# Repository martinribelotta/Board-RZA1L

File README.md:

RZ/A1L Board
============

Cortex-A9 board for Renesas RZ CPU using KiCAD

Hardware
--------

 - **CPU**: RZ/A1L 208LQFP
 - **RAM**: 32/64M sdram
 - **Flash**: 16/32M QSPI FLASH
 - **VGA**: 24bpp@\<TBD\>Hz
 - **USB**: 1 Host & 1 Dev
 - **GPIO**: 30 GPIO (+6 LED +2 Button) Muxed with:

Block Diagram
-------------

Schematic
---------

Preview
-------

Top view

Bottom view

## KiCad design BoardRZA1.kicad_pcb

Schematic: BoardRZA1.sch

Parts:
C1, C2, C3, C4, C5, C6, C7, C8, C11, C13, C14, C15, C16, C17, C18, C19, C21, C23, C24, C25, C26, C28, C29, C30, C31, C32, C33, C34, C35, C38, C39, C40, C41, C42, C43, C44, C45, C51, C52: 100n; C_0805
C36, C37: 10p; C_0805
C46, C50, C53: 1u; C_0805
C48, C67, C68, C69, C70, C71: 10u; C_0805
C72, C73, C74, C75, C76: 100p; C_0805
CON1: USB-MINI-B; USB_MINI_B
CON2: USB-A-PCB; USB_A_Vertical
CON3: microSD
D1, D2, D3, D4, D7, D8: LED; LED-0805
L1, L2, L3, L4, L5, L6, L7, L8, L9: BLM18PG600; SM0805
P1: CONN_02X04; Pin_Header_Straight_2x04
P2, P3, P4, P5, P6, P7, P8, P9, P10, P11, P12, P13, P14, P15, P16, P17: CONN_1; PINTST
P18, P19: CONN_01X40; Pin_Header_Straight_2x20
R1: 5K6; R_0805
R2, R3, R51: 220R; R_0805
R4, R5, R6, R7, R8, R9, R10, R11, R12, R19, R20, R22, R23, R42, R43, R44, R50: 10k; R_0805
R27, R45, R46, R47, R48: 1k; R_0805
SW1: RESET; RigthAnglePush
SW2: NMI; RigthAnglePush
SW3: SW0; RigthAnglePush
SW4: SW1; RigthAnglePush
U1: RZ-A1L; PQFP208
U2: 13MHz; OSC_2x2p5
U3: 48MHz; OSC_4PIN
U4: N25QXXX; SOP2-8
U5: AS4C16M16S; TSOP_II_54
U6: NCP1117ST33T3G; sot223
U7: BU42xx; SSOP-5
U9: NCP1117ST12T3G; sot223
X1: 32.768k; Crystal_Round_Vertical_3mm

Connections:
+1.2V: C50.1, L5.2, L6.2, L7.2, L8.2, L9.2, P9.1, U9.2 (VO)
+3.3V: C34.1, C35.1, C38.1, C39.1, C40.1, C41.1, C42.1, C43.1, C44.1, C45.1, C46.1, C51.1, C72.1, CON3.4 (VDD), D1.2 (K), D2.2 (K), D3.2 (K), D4.2 (K), D7.2 (K), D8.2 (K), L1.1, L2.1, L3.1, L4.1, P6.1, P18.3, P18.4, P18.37, P18.38, P19.3, P19.4, P19.37, P19.38, R4.1, R5.1, R6.1, R7.1, R8.1, R11.1, R19.1, R20.2, R22.1, R42.2, R43.2, R44.2, U2.4 (VCC), U3.4 (VCC), U4.8 (VCC), U5.1 (VDD), U5.3 (VDDQ), U5.9 (VDDQ), U5.14 (VDD), U5.27 (VDD), U5.43 (VDDQ), U5.49 (VDDQ), U6.2 (VO), U7.2 (Vdd), U9.3 (VI)
/+5v: C48.1, CON1.1 (VBUS), CON2.1 (VBUS), P2.1, U1.169 (VBUSIN1), U1.176 (VBUSIN0), U6.3 (VI)
/AVcc: C3.1, C33.2, L2.2, U1.102 (AVCC), U1.104 (AVref)
/DM_CLK: R10.2, U1.81 (P0_2/MD_CLK/RxD1/IRQ7)
/D_D+: CON1.3 (D+), U1.175 (DP0)
/D_D-: CON1.2 (D-), U1.174 (DM0)
/H_D+: CON2.3 (D+), U1.168 (DP1)
/H_D-: CON2.2 (D-), U1.167 (DM1)
/JTAG_TCK: P1.2, R7.2, U1.117 (TCK)
/JTAG_TDI: P1.6, R8.2, U1.115 (JP0_0/TDI)
/JTAG_TDO: P1.4, R5.2, U1.114 (JP0_1/TDO)
/JTAG_TMS: P1.1, R4.2, U1.116 (TMS)
/JTAG_TRST: P1.8, R6.2, R50.2, U1.113 (TRST)
/LCD_DATA0: P18.19, U1.192 (P8_0/LCD0_DATA0/ET_TXD0/SSISCK1/SCK3)
/LCD_DATA1: P18.20, U1.194 (P8_1/LCD0_DATA1/ET_TXD1/SSIWS1/RxD3)
/LCD_DATA2: P18.21, U1.198 (P8_2/LCD0_DATA2/ET_TXD2/SSITxD1/TxD3)
/LCD_DATA3: P18.22, U1.199 (P8_3/LCD0_DATA3/ET_TXD3/SSIRxD1)
/LCD_DATA4: P18.23, U1.200 (P8_4/LCD0_DATA4/ET_TXCLK/CTS2/TIOC0A)
/LCD_DATA5: P18.24, U1.201 (P8_5/LCD0_DATA5/ET_TXER/RTS2/TIOC0B)
/LCD_DATA6: P18.31, U1.27 (P8_6/LCD0_DATA6/ET_TXEN/IRQ6/CTS1/TIOC0C)
/LCD_DATA7: P18.32, U1.28 (P8_7/LCD0_DATA7/ET_RXD0/IRQ7/RTS1/TIOC0D)
/LCD_DATA8: P18.25, U1.17 (P6_0/D16/LCD0_DATA8/RSPCK0/TCLKA/WDTOVF)
/LCD_DATA9: P18.26, U1.19 (P6_1/D17/LCD0_DATA9/SSL00/TCLKB)
/LCD_DATA10: P18.27, U1.20 (P6_2/D18/LCD0_DATA10/MOSI0/TCLKC)
/LCD_DATA11: P18.28, U1.22 (P6_3/D19/LCD0_DATA11/MISO0/TCLKD)
/LCD_DATA12: P18.29, U1.24 (P6_4/D20/LCD0_DATA12/SSISCK3/MLB_CLK)
/LCD_DATA13: P18.30, U1.26 (P6_5/D21/LCD0_DATA13/SSIWS3/MLB_SIG)
/LCD_DATA14: P18.35, U1.31 (P6_6/D22/LCD0_DATA14/SSITxD3/MLB_DAT)
/LCD_DATA15: P18.36, U1.32 (P6_7/D23/LCD0_DATA15/SSIRxD3/IRQ0/TIOC3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)
/LCD_DATA16: P19.5, U1.33 (P6_8/D24/LCD0_DATA16/SSISCK0/IRQ1/TIOC3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)
/LCD_DATA17: P19.8, U1.38 (P6_9/D25/LCD0_DATA17/SSIWS0/IRQ2/TIOC3C)
/LCD_DATA18: P19.9, U1.40 (P6_10/D26/LCD0_DATA18/SSITxD0/IRQ3/TIOC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)
/LCD_DATA19: P19.10, U1.41 (P6_11/D27/LCD0_DATA19/SSIRxD0/SSI_DATA2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)
/LCD_DATA20: P19.11, U1.43 (P6_12/D28/LCD0_DATA20/RSPCK1/SSI_SCK2/R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)
/LCD_DATA21: P19.12, U1.46 (P6_13/D29/LCD0_DATA21/SSL10/SSI_WS2/CTS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)
/LCD_DATA22: P19.13, U1.48 (P6_14/D30/LCD0_DATA22/MOSI1/SSI_DATA2/R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)
/LCD_DATA23: P19.14, U1.49 (P6_15/D31/LCD0_DATA23/MISO1/TxD0/DV0_DA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)
/LCD_HSYNC: P18.33, U1.29 (P8_8/LCD0_TCON0/ET_RXD1/AUDIO_XOUT/SCK2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)
/LCD_PCLK: P19.19, U1.55 (P7_4/WAIT/MMC_CLK/SD_CLK_1/IETxD/LCD0_C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)
/LCD_VSYNC: P18.34, U1.30 (P8_9/LCD0_TCON1/ET_RXD2/CAN1TX/RxD2/AUD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)
/LED0: P19.7, R45.1, U1.35 (P8_10/LCD0_TCON2/ET_RXD3/CAN1RX/TxD2)
/LED1: P19.6, R46.1, U1.37 (P8_11/LCD0_TCON3/SSISCK2/SCK4)
/LED2: P19.15, R47.1, U1.50 (P7_0/LCD0_EXTCLK/MMC_CD/SD_CD_1/SPDIF_O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)
/LED3: P19.16, R48.1, U1.51 (P7_1/CS1/AUDIO_XOUT/SD_WP_1/TxD2/DV0_DA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)
/LED4: P19.17, R27.1, U1.52 (P7_2/CS4/MMC_D1/SD_D1_1/IRQ4/CAN0RX/DV0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)
/MD_BOOT0: R12.2, U1.79 (P0_0/MD_BOOT0/RxD0/IRQ4)
/MD_BOOT1: R11.2, U1.80 (P0_1/MD_BOOT1/RxD2/SSIRxD3/ADTRG)
/MD_CLKS: R9.2, U1.82 (P0_3/MD_CLKS/RxD3/SPDIF_IN)
/NMI: P19.27, R42.1, SW2.1, U1.90 (NMI)
/P1_0: P18.5, U1.149 (P1_0/RIIC0SCL/IRQ4/ET_RXD0/DV0_DATA0)
/P1_1: P18.6, U1.150 (P1_1/RIIC0SDA/IRQ5/ET_RXD1/DV0_DATA1)
/P1_2: P18.7, U1.151 (P1_2/RIIC1SCL/IRQ6/ET_RXD2/DV0_DATA2)
/P1_3: P18.8, U1.152 (P1_3/RIIC1SDA/IRQ7/ET_RXD3/DV0_DATA3)
/P1_4: P18.9, U1.153 (P1_4/RIIC2SCL/IRQ0/DREQ0/VIO_D0)
/P1_5: P18.10, U1.154 (P1_5/RIIC2SDA/IRQ1/VIO_D1)
/P1_6: P18.11, U1.155 (P1_6/RIIC3SCL/IRQ2/SSIRxD0/VIO_D2)
/P1_7: P18.12, U1.156 (P1_7/RIIC3SDA/IRQ3/RxD2/VIO_D3)
/P1_8: P19.29, U1.94 (P1_8/AN0/IRQ0/RxD0/DV0_DATA4)
/P1_9: P19.30, U1.95 (P1_9/AN1/IRQ1/RxD1/DV0_DATA5)
/P1_10: P19.31, U1.96 (P1_10/AN2/IRQ2/RxD2/DV0_DATA6)
/P1_11: P19.32, U1.97 (P1_11/AN3/IRQ3/RxD3/DV0_DATA7)
/P1_12: P19.33, U1.98 (P1_12/AN4/IRQ4/ET_RXD0/VIO_D4)
/P1_13: P19.34, U1.99 (P1_13/AN5/IRQ5/ET_RXD1/VIO_D5)
/P1_14: P19.35, U1.100 (P1_14/AN6/IRQ6/ET_RXD2/VIO_D6)
/P1_15: P19.36, U1.101 (P1_15/AN7/IRQ7/ET_RXD3/VIO_D7)
/P2_7: P18.14, U1.159 (P2_7/CS0/SSISCK3/TIOC1A/IRQ2)
/P2_8: P18.15, U1.160 (P2_8/RD/SSITxD3/TIOC0A/CAN0TX)
/P2_9: P18.16, U1.161 (P2_9/A0/SSIWS3/SCK0/IRQ1/CAN0RX)
/P3_15: P18.13, U1.157 (P3_15/A16/VIO_FLD/DV0_DATA15/TxD1)
/P7_3: P19.18, U1.53 (P7_3/CS5/MMC_D0/SD_D0_1/IRQ3/CAN0TX/DV0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)
/P7_5: P19.20, U1.56 (P7_5/BS/MMC_CMD/SD_CMD_1/TxD0/IERxD/LCD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)
/P7_6: P19.21, U1.57 (P7_6/WE2|DQMUL/MMC_D3/SD_D3_1/IRQ6/CTS2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)
/P7_7: P19.22, U1.59 (P7_7/WE3|DQMUU|AH/MMC_D2/SD_D2_1/IRQ5/R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)
/P7_8: P19.23, U1.60 (P7_8/CS2/SSISCK1/DV0_CLK/IRQ3/TxD0)
/P7_9: P19.24, U1.61 (P7_9/A25/SSIWS1/DV0_VSYNC/IRQ5/SCK3/TIO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)
/P7_10: P19.25, U1.62 (P7_10/TEND0/SSITxD1/DV0_HSYNC/RxD3)
/P7_11: P19.26, U1.63 (P7_11/DACK0/SSIRxD1/CAN_CLK/SCK2/TxD3/A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)
/P8_12(RXD): P1.3, U1.64 (P8_12/LCD0_TCON4/SPDIF_IN/SSIWS2/RxD4)
/P8_13(TXD): P1.5, U1.66 (P8_13/LCD0_TCON5/SPDIF_OUT/SSI_DATA2/Tx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)
/PLLVCC: C28.1, C76.1, L6.1, U1.85 (PLLVCC)
/PVCC: C5.1, C6.1, C7.1, C8.1, C11.1, C13.1, C14.1, C15.1, C16.1, C18.1, C19.1, C21.1, C69.1, C71.1, C73.1, C74.1, L1.2, P7.1, U1.11 (PVCC), U1.25 (PVCC), U1.36 (PVCC), U1.47 (PVCC), U1.58 (PVCC), U1.67 (PVCC), U1.78 (PVCC), U1.93 (PVCC), U1.106 (PVCC), U1.125 (PVCC), U1.130 (PVCC), U1.136 (PVCC), U1.147 (PVCC), U1.195 (PVCC), U1.206 (PVCC); also elsewhere on the board
/RAM_A1: U1.119 (P3_0/A1/SD_D2_0/LCD0_DATA0/ET_TXCLK), U5.23 (A0)
/RAM_A2: U1.120 (P3_1/A2/SD_D3_0/LCD0_DATA1/ET_TXER), U5.24 (A1)
/RAM_A3: U1.122 (P3_2/A3/SD_CMD_0/LCD0_DATA2/ET_TXEN), U5.25 (A2)
/RAM_A4: U1.124 (P3_3/A4/SD_CLK_0/LCD0_DATA3/ET_RXCLK), U5.26 (A3)
/RAM_A5: U1.126 (P3_4/A5/SD_D0_0/LCD0_DATA4/ET_RXER), U5.29 (A4)
/RAM_A6: U1.131 (P3_5/A6/SD_D1_0/LCD0_DATA5/ET_RXDV), U5.30 (A5)
/RAM_A7: U1.132 (P3_6/A7/SD_WP_0/LCD0_DATA6/ET_COL), U5.31 (A6)
/RAM_A8: U1.133 (P3_7/A8/SD_CD_0/LCD0_DATA7/ET_CRS), U5.32 (A7)
/RAM_A9: U1.138 (P3_8/A9/AUDIO_CLK/DV0_DATA8/SCK3), U5.33 (A8)
/RAM_A10: U1.139 (P3_9/A10/SPDIF_OUT/DV0_DATA9/TxD3), U5.34 (A9)
/RAM_A11: U1.141 (P3_10/A11/SPBIO_01_0/TIOC3B/DV0_DATA10/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), U5.22 (A10/AP)
/RAM_A12: U1.142 (P3_11/A12/SPBIO_11_0/TIOC3A/DV0_DATA11), U5.35 (A11)
/RAM_A13: U1.144 (P3_12/A13/SPBIO_21_0/TIOC3C/DV0_DATA12), U5.36 (A12)
/RAM_A14: U1.146 (P3_13/A14/SPBIO_31_0/TIOC3D/DV0_DATA13), U5.20 (BA0)
/RAM_A15: U1.148 (P3_14/A15/VIO_CLK/SPDIF_IN/DV0_DATA14/S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), U5.21 (BA1)
/RAM_CAS: U1.75 (P2_2/CAS/CAN1RX/TIOC0C/IRQ5), U5.17 (CAS#)
/RAM_CKE: U1.76 (P2_3/CKE/CAN1TX/TIOC0D), U5.37 (CKE)
/RAM_CLK: P5.1, U1.45 (CKIO), U5.38 (CLK)
/RAM_CS: U1.68 (P2_0/CS3/RLIN30_RX/SPDIF_IN/IRQ7), U5.19 (CS#)
/RAM_D0: U1.205 (P5_0/D0/MMC_D4/ET_TXD0/DV0_DATA16/LCD0_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), U5.2 (DQ0)
/RAM_D1: U1.207 (P5_1/D1/MMC_D5/ET_TXD1/DV0_DATA17/LCD0_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), U5.4 (DQ1)
/RAM_D2: U1.208 (P5_2/D2/MMC_D6/ET_TXD2/DV0_DATA18/LCD0_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), U5.5 (DQ2)
/RAM_D3: U1.1 (P5_3/D3/MMC_D7/ET_TXD3/DV0_DATA19/LCD0_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), U5.7 (DQ3)
/RAM_D4: U1.2 (P5_4/D4/RSPCK2/SSISCK1/DV0_DATA20), U5.8 (DQ4)
/RAM_D5: U1.3 (P5_5/D5/SSL20/SSIWS1/DV0_DATA21), U5.10 (DQ5)
/RAM_D6: U1.4 (P5_6/D6/MOSI2/SSITxD1/DV0_DATA22/SCK2), U5.11 (DQ6)
/RAM_D7: U1.5 (P5_7/D7/MISO2/SSIRxD1/DV0_DATA23/TxD2), U5.13 (DQ7)
/RAM_D8: U1.6 (P5_8/D8/CAN0RX/TIOC4A/IRQ3), U5.42 (DQ8)
/RAM_D9: U1.8 (P5_9/D9/CAN0TX/TIOC4B/IRQ4), U5.44 (DQ9)
/RAM_D10: U1.10 (P5_10/D10/IERxD/TIOC4C/IRQ5), U5.45 (DQ10)
/RAM_D11: U1.12 (P5_11/D11/IETxD/TIOC4D/IRQ6), U5.47 (DQ11)
/RAM_D12: U1.13 (P5_12/D12/SSISCK2/SCK4/AUDIO_XOUT2), U5.48 (DQ12)
/RAM_D13: U1.14 (P5_13/D13/SSIWS2/AUDIO_XOUT/AUDIO_XOUT3), U5.50 (DQ13)
/RAM_D14: U1.15 (P5_14/D14/SSI_DATA2/RxD4/TIOC2A), U5.51 (DQ14)
/RAM_D15: U1.16 (P5_15/D15/SD_WP_1/TxD4), U5.53 (DQ15)
/RAM_DQMH: U1.112 (P2_5/WE1|WE|DQMLU/TIOC3A), U5.39 (UDQM)
/RAM_DQML: U1.110 (P2_4/WE0|DQMLL/TIOC4A), U5.15 (LDQM)
/RAM_RAS: U1.69 (P2_1/RAS/RLIN30_TX/SPDIF_OUT/IRQ6), U5.18 (RAS#)
/RAM_RDnWR: U1.158 (P2_6/RD_nWR/SSIRxD3/TIOC2A), U5.16 (WE#)
/RESET: C53.2, P19.28, R20.1, SW1.1, U1.92 (RES), U7.1 (Vout)
/SD_CD_1: CON3.G5 (DET), R19.2, U1.70 (P8_14/LCD0_TCON6/ET_COL/SD_CD_0/SCK1)
/SD_CLK_1: CON3.5 (CLK), U1.127 (P9_2/RSPCK2/ET_RXCLK/SD_CLK_0/RTS0/TIOC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)
/SD_CMD_1: CON3.3 (CMD), U1.129 (P9_3/SSL20/ET_RXER/SD_CMD_0/SCK0/TIOC1B)
/SD_D0_1: CON3.7 (DAT0), U1.73 (P9_1/ET_MDIO/SD_D0_0/CTS0)
/SD_D1_1: CON3.8 (DAT1), U1.72 (P9_0/ET_MDC/SD_D1_0/TxD1)
/SD_D2_1: CON3.1 (DAT2), U1.137 (P9_5/MISO2/SD_D2_0/TxD0/TIOC2B)
/SD_D3_1: CON3.2 (CD/DAT3), U1.135 (P9_4/MOSI2/ET_RXDV/SD_D3_0/RxD0/TIOC2A)
/SPBCLK_0: U1.196 (P4_4/A21/SPBCLK_0/TRACE/CLK), U4.6 (CLK)
/SPBIO_00_0: U1.202 (P4_6/A23/SPBIO_00_0/TRACE/DATA0), U4.5 (DQ0)
/SPBIO_10_0: U1.204 (P4_7/A24/SPBIO_10_0/TRACE/DATA1), U4.2 (DQ1)
/SPBIO_20_0: U1.190 (P4_2/A19/SPBIO_20_0/TRACE/DATA2), U4.3 (nW/VPP/DQ2)
/SPBIO_30_0: U1.191 (P4_3/A20/SPBIO_30_0/TRACE/DATA3), U4.7 (nHOLD/DQ3)
/SPBSSL_0: U1.197 (P4_5/A22/SPBSSL_0/TRACE/CTL), U4.1 (nSSEL)
/SW0: P18.17, R43.1, SW3.1, U1.188 (P4_0/A17/VIO_VD/TIOC1B/ET_MDC/CTS1)
/SW1: P18.18, R44.1, SW4.1, U1.189 (P4_1/A18/VIO_HD/TIOC2B/ET_MDIO/RTS1)
/SYS_CLK: P4.1, R2.1, U1.86 (EXTAL)
/USBAPVCC: C2.1, C67.1, L4.2, U1.181 (USBAPVCC)
/USBAVCC: C29.1, L7.1, U1.182 (USBAVCC)
/USBDPVCC: C1.1, C4.1, C68.1, L3.2, U1.165 (USBDPVCC), U1.172 (USBDPVCC)
/USBDVCC: C31.1, C32.1, L9.1, U1.170 (USBDVCC), U1.177 (USBDVCC)
/USBUVCC: C30.1, L8.1, U1.184 (USBUVCC)
/USB_CLK: P3.1, R3.1, U1.163 (USB_X1)
/VCC: C17.1, C23.1, C24.1, C25.1, C26.1, C70.1, C75.1, L5.1, P8.1, U1.7 (VCC), U1.21 (VCC), U1.42 (VCC), U1.74 (VCC), U1.111 (VCC), U1.121 (VCC), U1.143 (VCC); also elsewhere on the board
unnamed: C36.2, U1.84 (RTC_X2), X1.1
unnamed: C37.2, U1.83 (RTC_X1), X1.2
unnamed: C52.1, U7.5 (CT)
unnamed: D1.1 (A), R45.2
unnamed: D2.1 (A), R46.2
unnamed: D3.1 (A), R47.2
unnamed: D4.1 (A), R48.2
unnamed: D7.1 (A), R51.2
unnamed: D8.1 (A), R27.2
unnamed: R1.2, U1.179 (REFRIN)
unnamed: R2.2, U2.3 (OUT)
unnamed: R3.2, U3.3 (OUT)
unnamed: R22.2, R23.2, U1.105 (BSCANP)
VSS: C1.2, C2.2, C3.2, C4.2, C5.2, C6.2, C7.2, C8.2, C11.2, C13.2, C14.2, C15.2, C16.2, C17.2, C18.2, C19.2, C21.2, C23.2, C24.2, C25.2, C26.2, C28.2, C29.2, C30.2, C31.2, C32.2, C33.1, C34.2, C35.2, C36.1, C37.1, C38.2, C39.2, C40.2, C41.2, C42.2, C43.2, C44.2, C45.2, C46.2, C48.2, C50.2, C51.2, C52.2, C53.1, C67.2, C68.2, C69.2, C70.2, C71.2, C72.2, C73.2, C74.2, C75.2, C76.2, CON1.5 (GND), CON1.6 (SHELL1), CON1.7 (SHELL2), CON1.8 (SHELL3), CON1.9 (SHELL4), CON2.4 (GND), CON3.6 (VSS), CON3.G1 (GND), CON3.G2 (GND), CON3.G3 (GND), CON3.G4 (POL), P1.7, P10.1, P11.1, P12.1, P13.1, P14.1, P15.1, P16.1, P17.1, P18.1, P18.2, P18.39, P18.40, P19.1, P19.2, P19.39, P19.40, R1.1, R9.1, R10.1, R12.1, R23.1, R50.1, R51.1, SW1.2, SW2.2, SW3.2, SW4.2, U1.9 (VSS), U1.18 (VSS), U1.23 (VSS), U1.34 (VSS), U1.39 (VSS), U1.44 (VSS), U1.54 (VSS), U1.65 (VSS), U1.77 (VSS), U1.88 (VSS), U1.89 (VSS), U1.91 (VSS), U1.103 (AVSS), U1.109 (VSS), U1.118 (VSS), U1.123 (VSS), U1.128 (VSS), U1.134 (VSS), U1.140 (VSS), U1.145 (VSS), U1.162 (VSS), U1.166 (USBDPVSS), U1.171 (USBDVSS), U1.173 (USBDPVSS), U1.178 (USBDVSS), U1.180 (USBAPVSS), U1.183 (USBAVSS), U1.185 (USBUVSS), U1.186 (VSS), U1.187 (VSS), U1.193 (VSS), U1.203 (VSS), U2.2 (GND), U3.2 (GND), U4.4 (VSS), U5.6 (VSSQ), U5.12 (VSSQ), U5.28 (VSS), U5.41 (VSS), U5.46 (VSSQ), U5.52 (VSSQ), U5.54 (VSS), U6.1 (GND), U7.3 (GND), U9.1 (GND); also elsewhere on the board

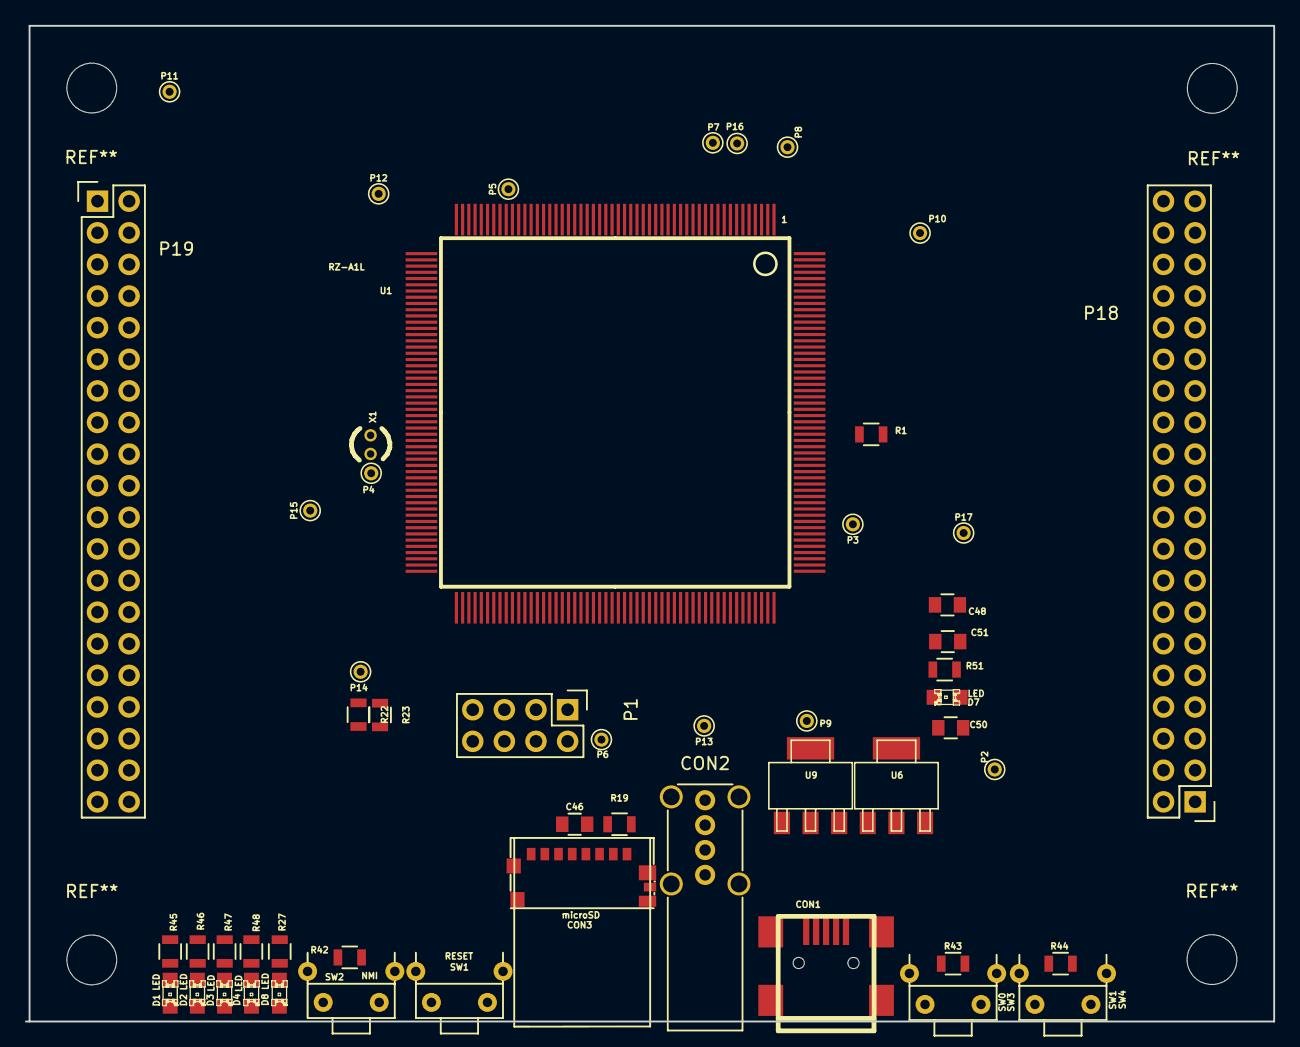
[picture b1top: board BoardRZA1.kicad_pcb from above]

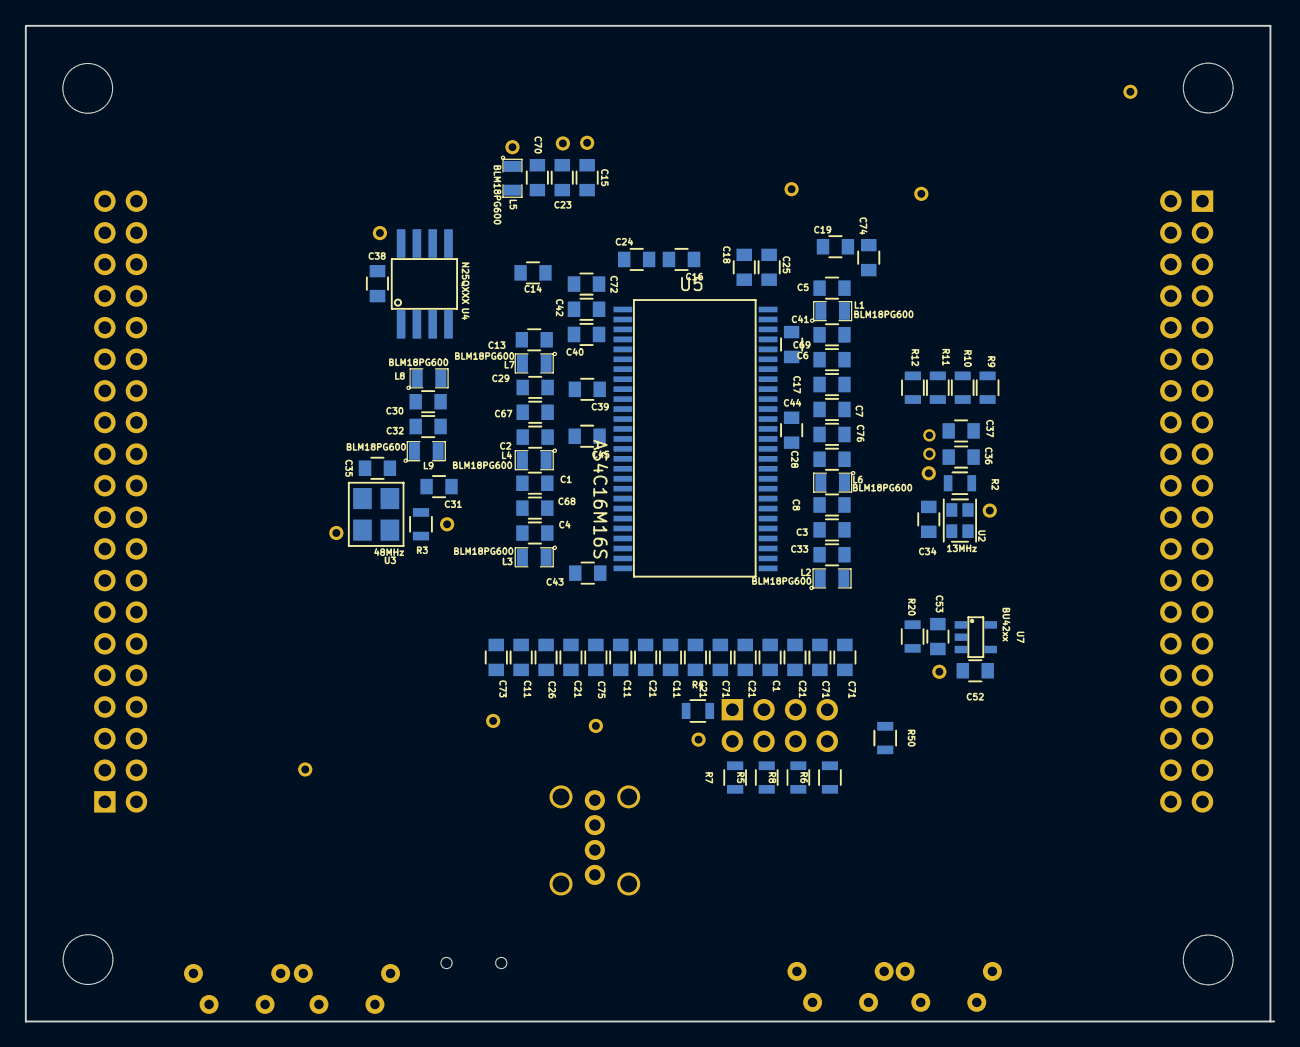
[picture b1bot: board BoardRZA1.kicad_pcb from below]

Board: 4 copper layers, 100.3 x 80.0 mm, 140 parts (87 on the bottom side), 159 nets, no tracks yet.

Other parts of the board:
C1#2, C11#2, C11#3, C21#2, C21#3, C21#4, C21#5: 100n; C_0805
C71#2, C71#3: 100p; C_0805

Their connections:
/PVCC: C1#2.1, C11#2.1, C11#3.1, C21#2.1, C21#3.1, C71#2.1; also elsewhere on the board
/VCC: C21#4.1, C21#5.1, C71#3.1; also elsewhere on the board
VSS: C1#2.2, C11#2.2, C11#3.2, C21#2.2, C21#3.2, C21#4.2, C21#5.2, C71#2.2, C71#3.2; also elsewhere on the board

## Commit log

2014-11-09 Readme and some images from kicad render
2014-11-09 Minor typo on README
2014-11-11 Ruteo de power. Reogranizado de la plaqueta y planos de masa
2014-11-11 Actualizado preview 3d
2014-11-15 Add ETH Add reset system Correct clock footprint Finish main routing and power/gnd planes
2014-11-16 GPIO routed
2014-11-18 Leds&buttons rerout eth out
2014-11-18 Cambia XTAL 25MHz Phy por OSC 25MHz
2014-11-19 USB-B CON2 -> USB-A CON2
2014-11-19 Stupid README images update
2014-11-20 Add power from mini usb-b Prettify 3D
2014-11-20 Logo & move some nets
2014-11-21 PHY OSC to XI fixed. Move some refs. Optional pulldown on TRST
2014-11-22 Add 10uF decouple on pvcc, vcc & 3v3
2014-11-24 Add 100pF C over power rails (700MHz filters) ERC pass DRC pass
2014-11-27 Arrangue PCB
2014-11-30 Correct U4 SOP2-8 package. Rearangue footprint libraries
2014-12-03 Add vias to decouple cap. over VSS.
2014-12-04 Add testpoints
2014-12-06 Arrange Sylkscreen
2014-12-13 Rearrange sylkscreen over GPIO connector
2014-12-17 Add serial connector over UART4. Add GPIO labels, update images
2014-12-17 Add block diagram
2014-12-17 Cosmetic changes
2014-12-28 Minor changes
2014-12-28 Arrange inner power planes
2014-12-28 Rework power planes (2)
2015-01-12 Clean schematic libreary
2015-01-31 Some minor changes to PCB
2015-01-31 Add PDF schematic
2015-03-03 Added VGA out, remove eth
2015-03-03 Resize board, move VGA connector and R2R DAC
2015-03-05 Some minor routing changes to probe new kicad assisted route
2015-03-08 Update diagrams and pictures (1)
2015-03-08 Actualized schematic
2015-03-09 Schametic
2015-03-20 Change R2R DAC for ADV7125 on LQFP48
2015-03-24 Minimal modifications
2015-03-31 VGA DAC R2R to monolitic
2015-03-31 Schematic SVG to PNG. README.md github not support SVG
2015-04-13 Change SD_*_1 to SD_*_0 because LCD0_CLK is overlapped by SD_CLK_1
2015-04-17 Move VGA connector, MicroSD connector, reasign GPIO
2015-04-23 Documentation and 3d views
2015-05-03 PCB minor modifications
2015-05-06 Replace monlitic dual regulator by two XX1117-Y.Z
2015-05-07 New Routing
2015-05-09 Minor touch of board
2015-05-09 Documentation
2015-05-09 Documentation, images and schematic updates
2015-05-09 Update readme (2)
2015-05-09 Update readme (3)
2015-06-16 Update board minor changes
2015-07-01 Gerber files in protel format
2015-12-03 Change SOP2-8 pad size
2016-10-23 Fix TSSOP II 54 SDRAM footprint
2016-10-24 Minor bugfix on PCB layout reimport
2016-10-30 Rework on minimize board
